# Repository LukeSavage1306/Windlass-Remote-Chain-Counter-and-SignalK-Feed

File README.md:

# Windlass Remote Control with Chain Counter and Signalk Feed

NOTE: As at mid November 2022 the code, pcb link, images etc are the latest version as described below, but I have yet to update the purchasing links  Should be done in next week or so.

Credit for the original version of this app goes to AK-Hombergers.

The current version:

* Is based on a Wemos D1 Mini (ESP8266) reading pulses from a conventional windlass chain sensor with WiFi access to effect control either directly in AP mode or via the boats main wifi in station mode.
* In AP mode uses mDNS for easy access via a named URL rather than remembering IP addresses
* Provides a wireless remote windlass control from any phone/tablet with wifi capability giving up/down/stop/chain-length-counter/counter-reset functionality and the ability to enter a preset scope to which the windlass will automatically raise/lower the chain.
* Provides chain-length to SignalK via a UDP connection
* Works with 12 volt systems - just requires a single transient suppressor diode to be changed for 24v 
* Will also track chain-length when the windlass is operated by existing controls or when allowed to "free fall"
* LED ON indicates that the board should be operating the windlass.  Off indicates board is in standby
* Stores current chain length in nonvolatile memory so that length is stored on switch off and restored after powering back up.
* Demo mode to check correct operation without need for a gypsy sensor present.
* Detects windlass operation from other existing controls and counts chain for up/down/free fall 

Includes various safety features:

- Safety interlock so that Up/Down will not work if another (existing) control is already operating the windlass.
- Safety stop to stop "anchor up" a preset number of gypsy revolutions before reaching zero (can be changed in code with SAFETY_STOP).
- Safety stop if maximum chain length is reached (can be changed with MAX_CHAIN_LENGTH)
- Safety watchdog timer to stop power after predetermined period of inactivity of client (e.g. due to loss of wifi connection).
- Safety watchdog timer to detect blocked chain. Windlass stops if no events are detected within predetermined period of activity after up/down command.

To implement you need to
* Build and install the windlass control board - PCB design available from the link below
* Configure the code (in Arduino)
   - WLAN type setting WiFiMode_AP_STA to "0" (stand alone access point) or "1" (Client with DHCP for SignalK feed).  Note code assumes SignalK server is at 10.10.10.1.  Configure to suit your set up.  More detail on this below.
   - Configure your wifi SSID and password
   - Calibrate for your sensor (e.g. 0.35 meter per revolution of the gypsy) and the maximum chain length
   - Flash the code to the ESP8266

If working as a standalone Access Point, connect the phone/tablet to the defined network (default SSID is "windlass", password "windlass" - can be changed at lines 23 and 24)  and browse to "windlass.local"  (can be changed at line 195)
If working as WLAN client, browsing to "windlass.local" should still work - although I haven't tested it.  If not determine the DHCP IP address using the Arduino Serial Monitor (or other IDE) and start your browser with that IP address.

This should give you a screen as per below on your phone/tablet.  A flashing red dot in the title bar indicates connection established with the Wemos.

To control the anchor chain relay just press:
- "Down" for anchor down
- "Up" for anchor up
- "Stop" for Stop
- "Reset" to reset the chain counter to zero
- Or enter the desired scope and hit "Target Scope" to pay out/pull in to the set length

A [pcb layout](https://github.com/LukeSavage1306/Windlass-Remote-Chain-Counter-and-SignalK-Feed/blob/main/24vD1MiniWindlassControlAndChainCounter.kicad_pcb) is available in the main folder. 

You can order a PCB from Aisler.net:  https://aisler.net/p/LRMWVSQR

## Parts:

Parts list currently points to largely German suppliers but are generally widely available with the exception of the PCB. If you want to source these elsewhere I can provide the detailed KiCad files. 

- Board [Link](https://aisler.net/p/ESKPZAUS)
- U1 D1 Mini [Link](https://www.reichelt.de/de/en/d1-mini-esp8266-v3-0-d1-mini-p253978.html?&nbc=1)
- U3 K7805 1000R3L [Link](https://uk.rs-online.com/web/p/switching-regulators/1934015/)
- C1 10uF 50v can electrolytic (can be reduced to 25v if running on a 12V system)
- C2 22uF 15v can electrolytic 
- R1 Resistor 5 KOhm (if using 12v you can reduce this to 2.2 Kohm to ensure accurate counting at low battery voltage) [Link](https://www.reichelt.de/de/en/carbon-film-resistor-1-4-w-5-1-0-kilo-ohms-1-4w-1-0k-p1315.html?&trstct=pos_2&nbc=1)
- R2, R3 Resistor 270 Ohm (*2) [Link](https://www.reichelt.de/de/en/carbon-film-resistor-1-4-w-5-270-ohm-1-4w-270-p1390.html?&nbc=1)
- R4, R5 Resistor 10 KOhm (*2) [Link](https://www.reichelt.de/de/en/carbon-film-resistor-1-4w-5-10-kilo-ohms-1-4w-10k-p1338.html?&nbc=1)
- Q1, Q2, Q3, Q4 Transistor BC337 (*4) [Link](https://www.reichelt.de/de/en/transistor-to-92-bl-npn-45v-800ma-bc-337-25-dio-p219125.html?&nbc=1)
- D2, D3 Diode 1N4148 (*2) [Link](https://www.reichelt.de/schalt-diode-100-v-150-ma-do-35-1n-4148-p1730.html?search=1n4148)
- D1 Diode 1N4001 [Link](https://www.reichelt.de/de/en/rectifier-diode-do41-50-v-1-a-1n-4001-p1723.html?&nbc=1)
- U2 H11-L1 [Link](https://www.reichelt.de/optokoppler-1-mbit-s-dil-6-h11l1m-p219351.html?search=H11-l1)
- K1, K2 Relay (*2) [Link](https://www.reichelt.de/de/en/miniature-power-relay-g5q-1-no-5-v-dc-5-a-g5q-1a-eu-5dc-p258331.html?&nbc=1)
- J1, J3, J4 Connector 2-pin (*3) [Link](https://www.reichelt.de/de/en/2-pin-terminal-strip-spacing-5-08-akl-101-02-p36605.html?&nbc=1)

The current design should work for a Quick or Lofrans anchor chain relay and chain sensor (which looks like a simple reed relay triggerd from a magnet). Connection details  for a Quick windlass/counter can be found here: https://www.quickitaly.com/resources/downloads_qne-prod/1/CHC1203_IT-EN-FR_REV001A.pdf

The board requires connection to your windlass power supply (12v - for 24v change the transient suppressor diode D4 for circa 29v equivalent - no other configuration necessary), connection to your windlass sensor (polarity of connection does not matter) and connection of the Up and Down relay feeds to the existing Up and Down terminals on the main windlass relay (note: the switching terminals that connect to any existing switch controls - NOT the motor output terminals).

To access via the main boat wifi or to send data to SignalK you need to set up in Station mode.  To do that set WiFIMode_AP_STA to 1 at line 21 and define the main boat wifi SSID and Password at lines 23 and 24.   Define the signalk server IP and port at lines 25 and 26.  In Signalk you muse also define a UDP connection.  Go to Server, Connections and define a new connection as per the picture below.  Match the port number to the number you used in the .ino code (default is 4210).  Once configured ChainLength should appear as a data item within the Data Browser.

The gauge display can be changed to mirror your particular chain length in index_html.h   The range is set at lines 133/134 and the coloured zones at line 144

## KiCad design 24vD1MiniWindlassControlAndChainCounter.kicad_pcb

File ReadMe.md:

This code builds on the work of AKHombergers original design.  In its current format it:

* Provides a wireless remote windlass control based on a Wemos D1 Mini (ESP8266) with up/down/stop/chaincounter/counter reset functionality
* Provides chainlength to SignalK via a UDP connection
* Works with 12 and 24 volt systems
* Will track chainlength when the windlass is operated by existing controls or when allowed to "free fall"

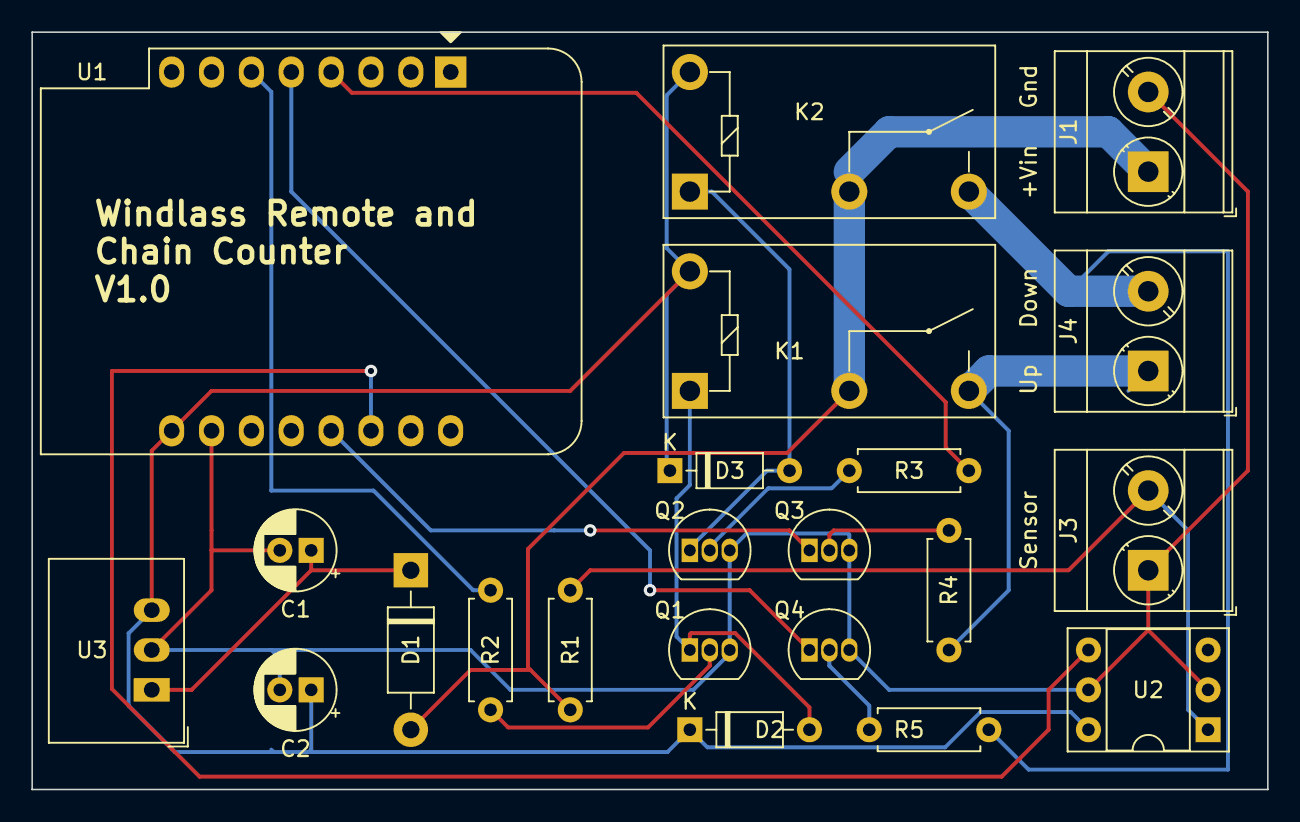
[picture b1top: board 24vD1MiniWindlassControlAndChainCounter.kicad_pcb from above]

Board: 2 copper layers, 78.7 x 48.3 mm, 22 parts (0 on the bottom side), 18 nets.

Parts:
C1: 10uF 50V; CP_Radial_D5.0mm_P2.00mm
C2: 22uF10V; CP_Radial_D5.0mm_P2.00mm
D1: 1N4001; D_DO-41_SOD81_P10.16mm_Horizontal
D2, D3: 1N4148; D_DO-35_SOD27_P7.62mm_Horizontal
J1: Power 12/24V; TerminalBlock_Phoenix_MKDS-3-2-5.08_1x02_P5.08mm_Horizontal
J3: Chain Sensor; TerminalBlock_Phoenix_MKDS-3-2-5.08_1x02_P5.08mm_Horizontal
J4: Chain Relay; TerminalBlock_Phoenix_MKDS-3-2-5.08_1x02_P5.08mm_Horizontal
K1, K2: G5Q-1A; Relay_SPST_Omron-G5Q-1A
Q1, Q2, Q3, Q4: BC337; TO-92_Inline
R1: 5k; R_Axial_DIN0207_L6.3mm_D2.5mm_P7.62mm_Horizontal
R2, R3: 270; R_Axial_DIN0207_L6.3mm_D2.5mm_P7.62mm_Horizontal
R4, R5: 10k; R_Axial_DIN0207_L6.3mm_D2.5mm_P7.62mm_Horizontal
U1: WeMos_D1_mini; WEMOS_D1_mini_light
U2: H11L1; DIP-6_W7.62mm_Socket
U3: K7805 1000R3L; Converter_DCDC_RECOM_R-78E-0.5_THT

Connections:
+5V: C2.1, D2.1, D3.1, K1.5, K2.5, U1.9, U2.6, U3.3
+12V: D1.2, J1.1, K1.2, K2.2, R1.1
GND: C1.2, C2.2, J1.2, J3.1, Q1.3, Q2.3, Q3.3, Q4.3, U1.10, U2.2, U2.5, U3.2
unnamed: C1.1, D1.1, U3.1
unnamed: D2.2, K1.1, Q1.1
unnamed: D3.2, K2.1, Q2.1
unnamed: J3.2, R1.2, U2.1
unnamed: J4.1, K1.3, R4.2
unnamed: J4.2, K2.3, R5.2
unnamed: Q1.2, R2.2
unnamed: Q2.2, R3.2
unnamed: Q3.1, U1.13
unnamed: Q3.2, R4.1
unnamed: Q4.1, U1.5
unnamed: Q4.2, R5.1
unnamed: R2.1, U1.6
unnamed: R3.1, U1.4
unnamed: U1.14, U2.4

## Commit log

2020-12-10 Create ChainCounter
2020-12-12 Update ChainCounter
2020-12-16 Create WIP chaincount
2020-12-16 Update WIP chaincount
2020-12-19 Rename ReadMe to ReadMe.Md
2020-12-19 Rename ReadMe.Md to ReadMe.md
2022-11-20 Updated version with new features and improved pcb
    Several enhancements including the ability to pay out or wind in to a pre-set scope, easier access from a browser using mDNS, improved board stability with transient voltage suppression
2022-11-20 Update README.md
    Outlined new features in V2.0
